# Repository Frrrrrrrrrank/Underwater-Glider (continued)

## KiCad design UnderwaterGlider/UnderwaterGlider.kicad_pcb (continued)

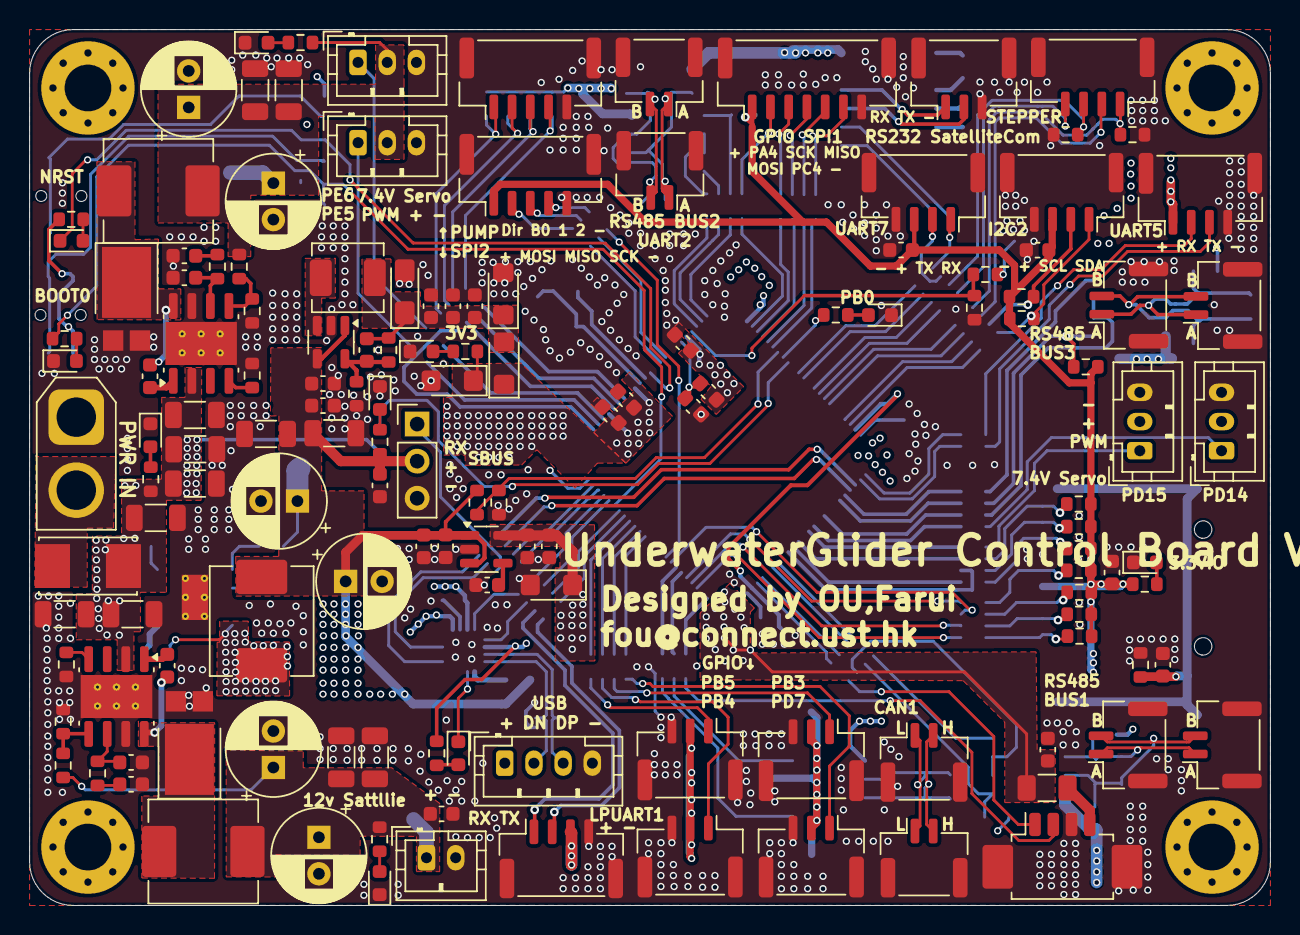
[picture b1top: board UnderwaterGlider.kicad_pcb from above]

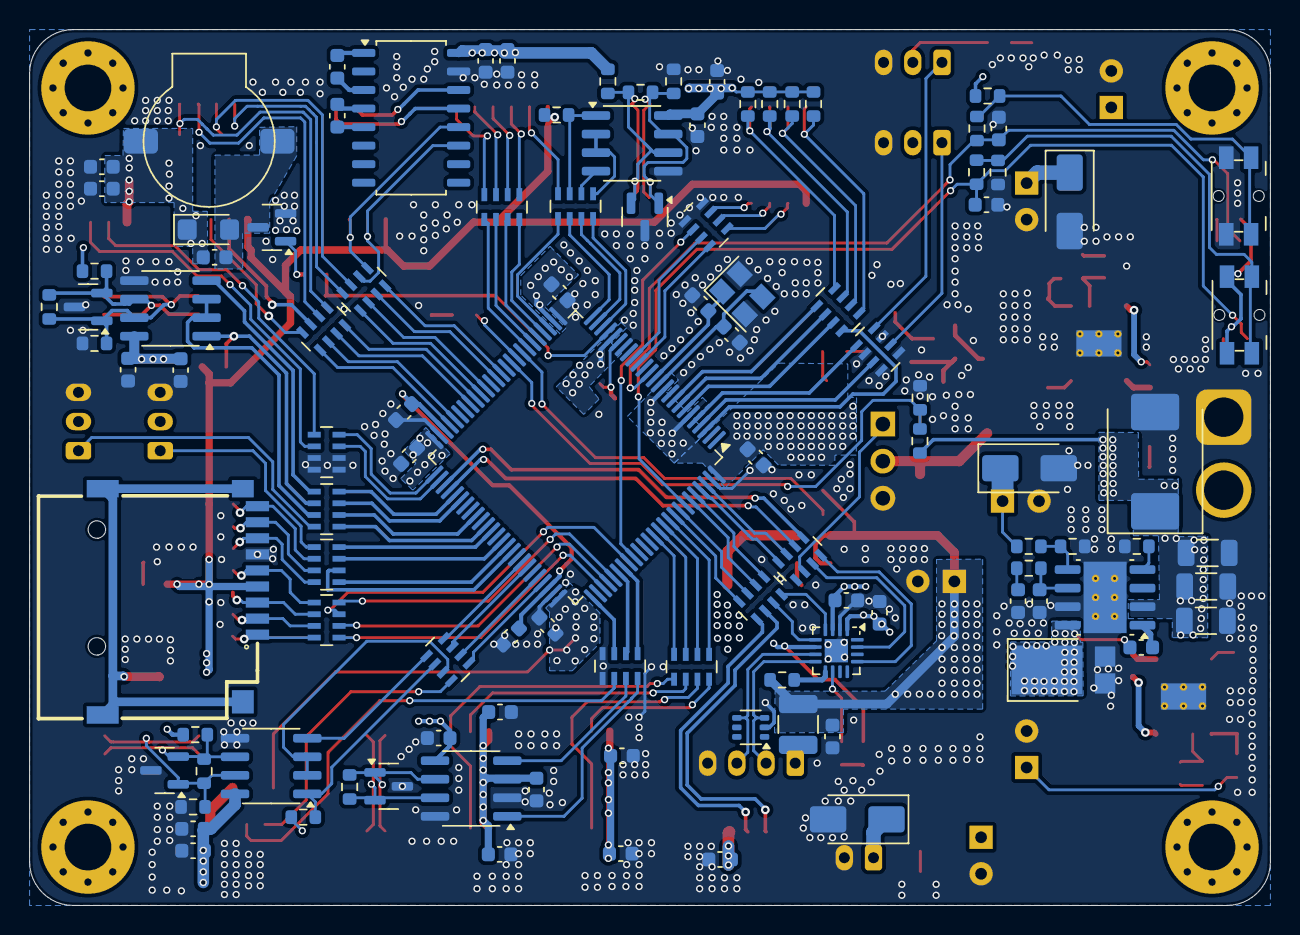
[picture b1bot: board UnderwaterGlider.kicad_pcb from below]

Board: 4 copper layers, 85.0 x 60.0 mm, 253 parts (108 on the bottom side), 190 nets.

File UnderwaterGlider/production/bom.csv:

Designator,Footprint,Quantity,Value,LCSC Part #
BZ2,MLT-9032,1,Buzzer,
"C1, C10, C11, C12, C125, C13, C16, C17, C18, C26, C37, C40, C52, C54, C55, C56, C57, C58, C59, C62, C7, C70, C71, C72, C73, C8, C81",0603,27,100n,
"C120, C121, C122, C123, C36, C39, C51, C53, C63, C64, C65, C66, C76, C84, C85, C86, C87, C88",0603,18,10u,
"C124, C126, C127, C27",0603,4,1u,
"C14, C15, C28, C29, C30, C31, C32, C33, C34, C35, C75, C77, C78, C82, C83",1206,15,10u,
C19,CP_EIA-3216-18_Kemet-A_Pad1.58x1.35mm_HandSolder,1,47u,
"C2, C25, C80",0603,3,47p,
"C20, C46",0603,2,0u1,
"C21, C22, C23, C47, C48, C49",CP_Radial_D6.3mm_P2.50mm,6,47u,
"C24, C3, C79",0603,3,4.7n,
C38,0603,1,10n,
"C50, C6, C67, C9",0603,4,20p,
"C60, C61",0603,2,2.2u,
D1,SOT-23,1,NUP2105L,
"D10, D8, D9",SOT-23,3,SM712,
"D11, D32, D33",0603,3,LED,
"D12, D13",D_SMF,2,DSS34,
"D15, D19",D_SMA,2,SMAJ5.0A,
"D16, D17",D_SMF,2,SMF3.3v,
D2,D_SMC,1,SMCJ28A,
D20,D_SMA,1,SMAJ7.5A,
D22,0603,1,LED_Red,
"D23, D27",0603,2,LED_Blue,
"D25, D30, D31",0603,3,LED_Green,
D26,0603,1,LED_Pink,
"D3, D4, D5",D_PowerDI-5,3,ST20100L,
D35,D_SMF,1,3V3 TVS,
F1,Fuseholder_Littelfuse_Nano2_157x,1,Fuse,
F2,1206,1,0.5A,
F3,1210,1,1.2A,
J1,TF-SMD_TF-PUSH,1,Micro_SD_Card_Det1,
J10,AMASS_XT30U-M_1x02_P5.0mm_Vertical,1,Conn_01x02,
"J11, J12, J13, J14, J15, J16, J17, J18",JST_GH_SM02B-GHS-TB_1x02-1MP_P1.25mm_Horizontal,8,Conn_01x02_MountingPin,
J19,JST_GH_BM04B-GHS-TBT_1x04-1MP_P1.25mm_Vertical,1,Conn_01x04_MountingPin,
J2,JST_PH_B2B-PH-K_1x02_P2.00mm_Vertical,1,Conn_01x02,
J20,JST_PH_B4B-PH-K_1x04_P2.00mm_Vertical,1,Conn_01x04,
"J21, J24, J3, J4",JST_GH_SM04B-GHS-TB_1x04-1MP_P1.25mm_Horizontal,4,Conn_01x04_MountingPin,
J22,PinHeader_1x03_P2.54mm_Vertical,1,SBus,
J23,JST_GH_BM07B-GHS-TBT_1x07-1MP_P1.25mm_Vertical,1,Conn_01x07_MountingPin,
"J25, J27",JST_GH_BM05B-GHS-TBT_1x05-1MP_P1.25mm_Vertical,2,Conn_01x05_MountingPin,
"J26, J29, J30, J31, J5",JST_GH_BM03B-GHS-TBT_1x03-1MP_P1.25mm_Vertical,5,Conn_01x03_MountingPin,
J28,Molex_PicoBlade_53261-0471_1x04-1MP_P1.25mm_Horizontal,1,SWD,
"J6, J7, J8, J9",JST_PH_B3B-PH-K_1x03_P2.00mm_Vertical,4,Conn_01x03,
"L1, L4, L5",L_Sunlord_MWSA0603S,3,7.2u,
L2,0603,1,220r,
L3,L_Sunlord_MWSA0402S,1,4u7,
Q1,SOT-23,1,AO3400A,
R1,0603,1,1M,
"R10, R14, R18, R2, R3, R36, R4, R40, R41, R43, R49, R59, R6, R61, R7, R70, R72, R78, R8, R83, R84, R9",0603,22,10k,
"R11, R13, R15, R17, R19, R21, R26, R46, R47, R48",0603,10,4k7,
"R12, R16, R20, R5",0603,4,120R,
"R22, R31, R32, R79, R80, R85, R86",0603,7,1k,
"R23, R58, R60",0603,3,330R,
"R24, R75",0603,2,100k,
"R25, R27, R28, R30",0603,4,4.7k,
"R33, R38, R45",0603,3,243k,
"R34, R37, R44",0603,3,16.9k,
R35,0603,1,47k,
R39,0603,1,53.6k,
R42,0603,1,33r,
R69,0603,1,140k,
R71,0603,1,82.5k,
"RN10, RN11, RN14, RN15, RN16, RN17, RN18, RN20, RN21, RN22, RN23, RN4, RN5, RN6, RN7, RN8",R_Array_Concave_4x0603,16,82R,
SW1,Panasonic_EVQPUL_EVQPUC,1,NRST,
SW2,Panasonic_EVQPUL_EVQPUC,1,BOOT0,
U1,LQFP-100_14x14mm_P0.5mm,1,STM32H743VITx,
U10,SOT-23-5,1,RS3236,
"U13, U14, U15",SOIC-8_3.9x4.9mm_P1.27mm,3,SN75176AD,
U16,TQFN-16-1EP_3x3mm_P0.5mm_EP1.6x1.6mm,1,CH343P,
U17,SOT-23-5,1,RY3430,
U2,SOIC-16_4.55x10.3mm_P1.27mm,1,MAX232,
U4,SOIC-8_3.9x4.9mm_P1.27mm,1,TJA1042T-3,
U6,SOT-363_SC-70-6,1,TPD4E1U06DCKR,
"U7, U8, U9",Texas_R-PDSO-G8_EP2.95x4.9mm_Mask2.4x3.1mm_ThermalVias,3,TPS54560BDDA,
Y1,Crystal_SMD_3225-4Pin_3.2x2.5mm,1,25MHz,

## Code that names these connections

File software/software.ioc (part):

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Mcu.Name=STM32H743VITx
Mcu.Package=LQFP100
Mcu.UserName=STM32H743VITx
PA0.Signal=S_TIM2_CH1_ETR
PA1.Mode=Hardware Flow Control (RS485)
PA1.Signal=USART2_DE
PA10.Mode=Asynchronous
PA10.Signal=USART1_RX
PA12.Mode=Hardware Flow Control (RS485)
PA12.Signal=USART1_DE
PA13\ (JTMS/SWDIO).Mode=Serial_Wire
PA13\ (JTMS/SWDIO).Signal=DEBUG_JTMS-SWDIO
PA14\ (JTCK/SWCLK).Mode=Serial_Wire
PA14\ (JTCK/SWCLK).Signal=DEBUG_JTCK-SWCLK
PA2.Mode=Asynchronous
PA2.Signal=USART2_TX
PA3.Mode=Asynchronous
PA3.Signal=USART2_RX
PA4.Mode=NSS_Signal_Hard_Output
PA4.Signal=SPI1_NSS
PA5.Mode=Full_Duplex_Master
PA5.Signal=SPI1_SCK
PA6.Mode=Full_Duplex_Master
PA6.Signal=SPI1_MISO
PA7.Mode=Full_Duplex_Master
PA7.Signal=SPI1_MOSI
PA9.Mode=Asynchronous
PA9.Signal=USART1_TX
PB0.GPIOParameters=GPIO_Label
PB0.GPIO_Label=LED
PB0.Signal=GPIO_Output
PB1.Signal=ADCx_INP5
PB10.Mode=I2C
PB10.Signal=I2C2_SCL
PB11.Mode=I2C
PB11.Signal=I2C2_SDA
PB12.Mode=Asynchronous
PB12.Signal=UART5_RX
PB13.Mode=Asynchronous
PB13.Signal=UART5_TX
PB14.Mode=CTS_RTS
PB14.Signal=UART4_RTS
PB15.Mode=CTS_RTS
PB15.Signal=UART4_CTS
PB3\ (JTDO/TRACESWO).GPIOParameters=GPIO_PuPd
PB3\ (JTDO/TRACESWO).GPIO_PuPd=GPIO_PULLUP
PB3\ (JTDO/TRACESWO).Signal=GPIO_Input
PB4\ (NJTRST).GPIOParameters=GPIO_PuPd
PB4\ (NJTRST).GPIO_PuPd=GPIO_PULLUP
PB4\ (NJTRST).Signal=GPIO_Input
PB5.GPIOParameters=GPIO_PuPd
PB5.GPIO_PuPd=GPIO_PULLUP
PB5.Signal=GPIO_Input
PB6.Mode=Asynchronous
PB6.Signal=LPUART1_TX
PB7.Mode=Asynchronous
PB7.Signal=LPUART1_RX
PB8.Mode=Asynchronous
PB8.Signal=UART4_RX
PB9.Mode=Asynchronous
PB9.Signal=UART4_TX
PC1.Mode=Full_Duplex_Master
PC1.Signal=SPI2_MOSI
PC10.Mode=SD_4_bits_Wide_bus
PC10.Signal=SDMMC1_D2
PC11.Mode=SD_4_bits_Wide_bus
PC11.Signal=SDMMC1_D3
PC12.Mode=SD_4_bits_Wide_bus
PC12.Signal=SDMMC1_CK
PC13.GPIOParameters=GPIO_PuPd,GPIO_Label,GPIO_ModeDefaultOutputPP
PC13.GPIO_Label=PUMP_SPEED_B0
PC13.GPIO_ModeDefaultOutputPP=GPIO_MODE_OUTPUT_PP
PC13.GPIO_PuPd=GPIO_NOPULL
PC13.Signal=GPIO_Output
PC14-OSC32_IN\ (OSC32_IN).GPIOParameters=GPIO_PuPd,GPIO_Label,GPIO_ModeDefaultOutputPP
PC14-OSC32_IN\ (OSC32_IN).GPIO_Label=PUMP_SPEED_B1
PC14-OSC32_IN\ (OSC32_IN).GPIO_ModeDefaultOutputPP=GPIO_MODE_OUTPUT_PP
PC14-OSC32_IN\ (OSC32_IN).GPIO_PuPd=GPIO_NOPULL
PC14-OSC32_IN\ (OSC32_IN).Signal=GPIO_Output
PC15-OSC32_OUT\ (OSC32_OUT).GPIOParameters=PinState,GPIO_PuPd,GPIO_Label,GPIO_ModeDefaultOutputPP
PC15-OSC32_OUT\ (OSC32_OUT).GPIO_Label=PUMP_STP
PC15-OSC32_OUT\ (OSC32_OUT).GPIO_ModeDefaultOutputPP=GPIO_MODE_OUTPUT_PP
PC15-OSC32_OUT\ (OSC32_OUT).GPIO_PuPd=GPIO_NOPULL
PC15-OSC32_OUT\ (OSC32_OUT).PinState=GPIO_PIN_SET
PC15-OSC32_OUT\ (OSC32_OUT).Signal=GPIO_Output
PC2_C.Mode=Full_Duplex_Master
PC2_C.Signal=SPI2_MISO
PC4.GPIOParameters=GPIO_Label
PC4.GPIO_Label=IMU_DRY
PC4.Signal=GPIO_Input
PC5.Signal=ADCx_INP8
PC7.Signal=GPIO_Input
PC8.Mode=SD_4_bits_Wide_bus
PC8.Signal=SDMMC1_D0
PC9.Mode=SD_4_bits_Wide_bus
PC9.Signal=SDMMC1_D1
PD0.Mode=FDCAN_Activate
PD0.Signal=FDCAN1_RX
PD1.Mode=FDCAN_Activate
PD1.Signal=FDCAN1_TX
PD12.Mode=Hardware Flow Control (RS485)
PD12.Signal=USART3_DE
PD14.Signal=S_TIM4_CH3
PD15.Signal=S_TIM4_CH4
PD2.Mode=SD_4_bits_Wide_bus
PD2.Signal=SDMMC1_CMD
PD3.Mode=Full_Duplex_Master
PD3.Signal=SPI2_SCK
PD7.GPIOParameters=GPIO_PuPd
PD7.GPIO_PuPd=GPIO_PULLUP
PD7.Signal=GPIO_Input
PD8.Mode=Asynchronous
PD8.Signal=USART3_TX
PD9.Mode=Asynchronous
PD9.Signal=USART3_RX
PE0.Mode=Asynchronous
PE0.Signal=UART8_RX
PE1.Mode=Asynchronous
PE1.Signal=UART8_TX
PE10.Signal=GPIO_Output
PE11.Signal=S_TIM1_CH2
PE12.Signal=GPIO_Output
PE13.Signal=GPIO_Output
PE14.Signal=S_TIM1_CH4
PE4.GPIOParameters=GPIO_PuPd,GPIO_Label,GPIO_ModeDefaultOutputPP
PE4.GPIO_Label=PUMP_DIR
PE4.GPIO_ModeDefaultOutputPP=GPIO_MODE_OUTPUT_PP
PE4.GPIO_PuPd=GPIO_NOPULL
PE4.Signal=GPIO_Output
PE5.Signal=S_TIM15_CH1
PE6.Signal=S_TIM15_CH2
PE7.Mode=Asynchronous
PE7.Signal=UART7_RX
PE8.Mode=Asynchronous
PE8.Signal=UART7_TX
PH0-OSC_IN\ (PH0).Mode=HSE-External-Oscillator
PH0-OSC_IN\ (PH0).Signal=RCC_OSC_IN
PH1-OSC_OUT\ (PH1).Mode=HSE-External-Oscillator
PH1-OSC_OUT\ (PH1).Signal=RCC_OSC_OUT
RCC.SYSCLKFreq_VALUE=100000000
RCC.SYSCLKSource=RCC_SYSCLKSOURCE_PLLCLK
board=custom

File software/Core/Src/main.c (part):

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  /* Initialize Ethernet UART driver on LPUART1 */
  EthernetUartDriver_Init(&hlpuart1);
  
  /* Initialize IMU module on UART5 (PB13 TX, PB12 RX). */
  IMU_Core_Init(&huart5);

  /* Initialize pressure sensor non-blocking RX driver */
  PressureSensorDriver_Init(&huart1);

  /* 尾舵使用 J9 / PD15 / TIM4_CH4：先写中位，再启动 333Hz PWM。 */
  if (RudderDriver_Init(&htim4) != HAL_OK)
  {
    Error_Handler();
  }
  g_dbg_servo_start_ok = 1U;

  /* Initialize thruster PWM driver on TIM15 CH1/CH2 (PE5/PE6). */
  if (ThrusterDriver_Init(&htim15) != HAL_OK)
  {
    Error_Handler();
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  /* Initialize SBUS non-blocking RX driver on UART8 */
  SbusDriver_Init(&huart8);

  /* Initialize buzzer PWM driver on TIM2 CH1 / PA0 */
  BuzzerDriver_Init(&htim2);
  {
    static const BuzzerTone init_done_tone[] = {
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  /*Configure GPIO pin Output Level */
  HAL_GPIO_WritePin(LED_GPIO_Port, LED_Pin, GPIO_PIN_RESET);

  /*Configure GPIO pins : PUMP_DIR_Pin PE10 PE12 PE13 */
  GPIO_InitStruct.Pin = PUMP_DIR_Pin|GPIO_PIN_10|GPIO_PIN_12|GPIO_PIN_13;
  GPIO_InitStruct.Mode = GPIO_MODE_OUTPUT_PP;
  GPIO_InitStruct.Pull = GPIO_NOPULL;
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  GPIO_InitStruct.Speed = GPIO_SPEED_FREQ_LOW;
  HAL_GPIO_Init(GPIOC, &GPIO_InitStruct);

  /*Configure GPIO pins : IMU_DRY_Pin PC7 */
  GPIO_InitStruct.Pin = IMU_DRY_Pin|GPIO_PIN_7;
  GPIO_InitStruct.Mode = GPIO_MODE_INPUT;
  GPIO_InitStruct.Pull = GPIO_NOPULL;
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  GPIO_InitStruct.Speed = GPIO_SPEED_FREQ_LOW;
  HAL_GPIO_Init(LED_GPIO_Port, &GPIO_InitStruct);

  /*Configure GPIO pin : PD7 */
  GPIO_InitStruct.Pin = GPIO_PIN_7;
  GPIO_InitStruct.Mode = GPIO_MODE_INPUT;
  GPIO_InitStruct.Pull = GPIO_PULLUP;
  HAL_GPIO_Init(GPIOD, &GPIO_InitStruct);

  /*Configure GPIO pins : PB3 PB4 PB5 */
  GPIO_InitStruct.Pin = GPIO_PIN_3|GPIO_PIN_4|GPIO_PIN_5;
  GPIO_InitStruct.Mode = GPIO_MODE_INPUT;
  GPIO_InitStruct.Pull = GPIO_PULLUP;
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* @note pitch 新机构安装方向修正：所有来源先按逻辑 RPM 仲裁，负数向机头、正数向机尾。
*       只在本任务最终调用 UMotor_SetTargetSpeedById 前乘一次 WORM_INSTALL_SIGN=-1。
*       键盘/手柄、SBUS、PID 和回零共用此处；不要在各入口或 PID 参数里重复补偿安装翻转。
*       驱动器实际正 RPM 向机头 PB4，负 RPM 向机尾 PD7，底层按此实际方向做限位。
*       回零逻辑 -350/+35 对应驱动器实际 +350/-35；原始位置反馈不取反。
*       g_rc_worm_cmd_rpm 和 UGWRM.cmd_rpm 记录转换后的驱动请求，便于对照原始反馈；
*       UGCTL.worm_rpm 仍是 PID 逻辑输出，二者符号不同不代表控制错误。
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
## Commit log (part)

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2026-01-09 init proj
2026-01-10 update layout
2026-01-19 update placement
2026-01-24 update version,submit custom
2026-03-05 update code, template with freeRTOS
2026-03-06 update code, with GNSS module testing
2026-03-10 update DYP test, successfully comm
2026-03-12 update RDSS test , decode with bug
2026-03-13 send short msg ok and return send ok,but platform cant receive
2026-03-16 ok,can transmit shortmsg of coordinate
2026-03-16 adding python script for decoding BDS msg
2026-03-24 read imu data ok
2026-03-25 update servo driver in main, wait to seperate in driver file
2026-04-01 ok to receive displacement sensor value
2026-04-10 can read UMotor
2026-04-16 fix resend BD shortmsg bug, can driver UMotor
2026-04-20 update pressure sensor
2026-04-20 update pressure sensor baud rate 115200
2026-04-21 update fs rc control, add test code in servoTask
2026-05-07 archive version, start hardware iteration
2026-05-07 start iteration of ver1.1
2026-05-07 ignore build outputs and KiCad temp files
2026-05-09 update schematic change
2026-05-11 update schematic design, ready to start layout
2026-05-12 update pcb from schematic
2026-06-01 finish layout , send manufature
2026-06-02 add ignore rules for build and KiCad temp files
2026-06-02 ok to control pump and linear displacement sensor feedback
2026-06-09 update can control pump, umotor,stepper, read displacement sensor, RC control at the same time
2026-06-09 update change ok for testing
2026-06-09 update hardware testing,12v tvs chosen wrong
2026-06-12 update delete temp file
2026-06-15 update pcb step model file
2026-06-15 add buzzer and led toggle pin
2026-06-16 update ethernet com, ok to send AT
2026-06-17 update ver1.1 stepper and pitch motor
2026-06-17 IMU加速度计输出单位更改
2026-06-17 change io control pump not yet test
2026-06-17 remove kicad lock files from integration
2026-06-18 ok to test pump
2026-06-18 imu and linear displacement sensor ok
2026-06-19 增加单独的TCPhandle
2026-06-19 测试版本,未修改cubemx
2026-06-22 完成限位开关闭环及线位移传感器闭环
2026-06-24 完成pitch由网线的控制，泵写完逻辑未调试
2026-06-24 网线可发送接受，但是存在bug有时会卡死，可能是因为数据包过大？
2026-06-24 修改python的上位机，现在网线通讯应该没有bug了
2026-06-24 增加了python的译码，但还未测试
2026-06-25 EKF面向嵌入式封装，架构完整，目前遇到活锁问题
2026-06-25 增加了推进器的控制，可能还要改下
2026-06-26 减小了从STM32发送至python端的数据包大小
2026-06-29 压力计失锁问题改正v1
2026-06-29 两个推进器分别控制
2026-06-30 IMU频率设置100hz，坐标系从FLU变换为FRD
2026-06-30 网口输出EKF状态估计量
2026-06-30 压力计频率调10HZ需要上机测试
2026-06-30 网口结构体调试出EKF参数
2026-06-30 EKF消息心跳包

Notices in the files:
software/Core/Src/main.c:
Copyright (c) 2026 STMicroelectronics.
All rights reserved.
This software is licensed under terms that can be found in the LICENSE file
